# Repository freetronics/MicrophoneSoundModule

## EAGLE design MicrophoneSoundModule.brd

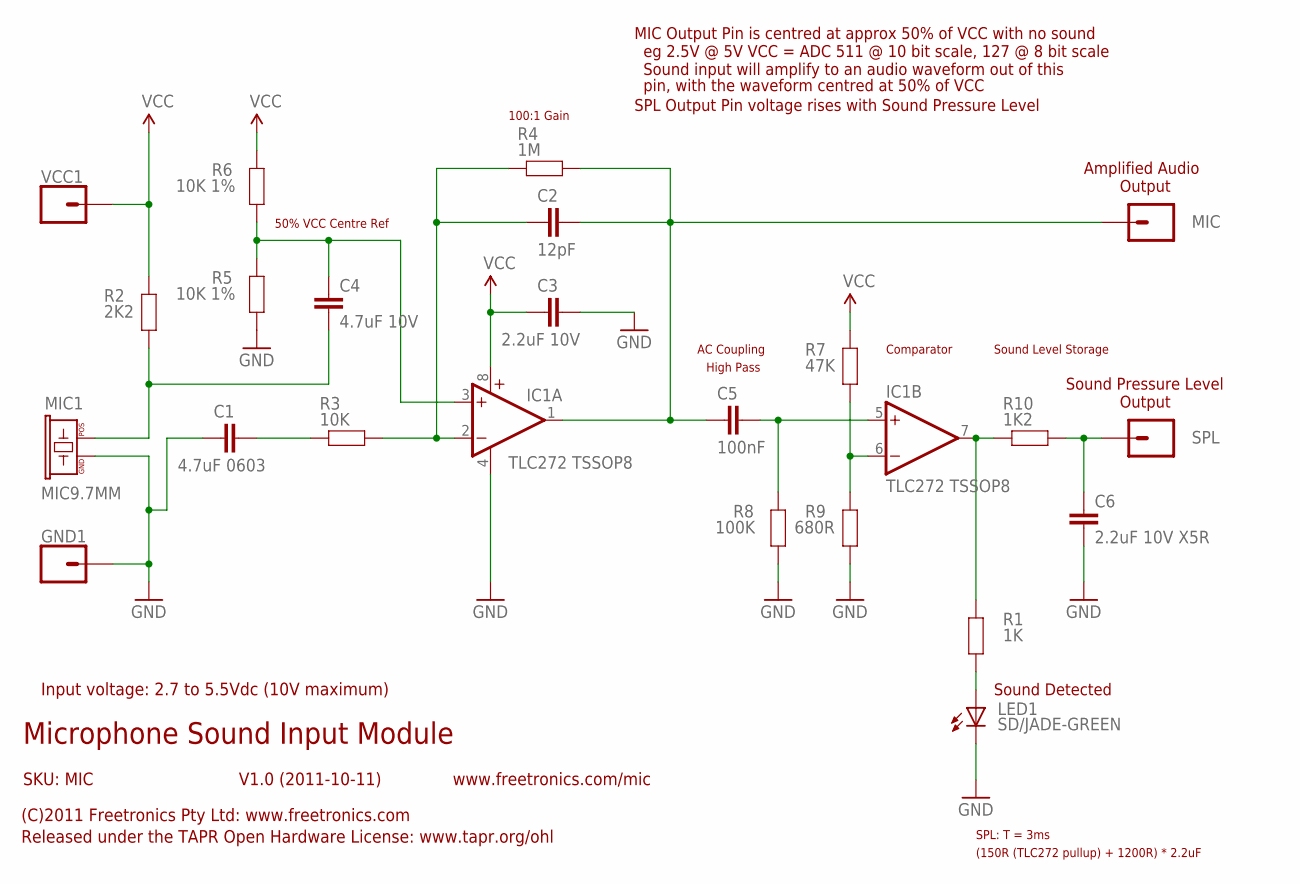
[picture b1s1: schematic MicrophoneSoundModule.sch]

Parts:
C1: 4.7uF 0603; 0603
C2: 12pF; 0603
C3: 2.2uF 10V; 0603
C4: 4.7uF 10V; 0603
C5: 100nF; 0603
C6: 2.2uF 10V X5R; 0603
GND1: M01PTH; 1X01
IC1: TLC272 TSSOP8; TSSOP8
LED1: SD/JADE-GREEN; LED-0603
MIC: M01PTH; 1X01
MIC1: MIC9.7MM; MIC-9.7MM
R1: 1K; 0603
R2: 2K2; 0603
R3: 10K; 0603
R4: 1M; 0603
R5, R6: 10K 1%; 0603
R7: 47K; 0603
R8: 100K; 0603
R9: 680R; 0603
R10: 1K2; 0603
SPL: M01PTH; 1X01
VCC1: M01PTH; 1X01

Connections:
GND: C1.1, C3.2, C6.1, GND1.1, IC1.4 (V-), LED1.C, MIC1.GND, R5.1, R8.1, R9.1
unnamed: LED1.A, R1.1
unnamed: C4.1, MIC1.POS, R2.1
unnamed: C1.2, R3.2
unnamed: C2.1, IC1.2 (-IN), R3.1, R4.2
unnamed: C2.2, C5.1, IC1.1 (OUT), MIC.1, R4.1
unnamed: C5.2, IC1.5 (+IN), R8.2
unnamed: C4.2, IC1.3 (+IN), R5.2, R6.1
unnamed: C6.2, R10.1, SPL.1
unnamed: IC1.6 (-IN), R7.1, R9.2
unnamed: IC1.7 (OUT), R1.2, R10.2
VCC: C3.1, IC1.8 (V+), R2.2, R6.2, R7.2, VCC1.1

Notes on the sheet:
Microphone Sound Input Module
V1.0 (2011-10-11)
SKU: MIC
(C)2011 Freetronics Pty Ltd: www.freetronics.com
Released under the TAPR Open Hardware License: www.tapr.org/ohl
www.freetronics.com/mic
Input voltage: 2.7 to 5.5Vdc (10V maximum)
50% VCC Centre Ref
100:1 Gain
MIC Output Pin is centred at approx 50% of VCC with no sound
eg 2.5V @ 5V VCC = ADC 511 @ 10 bit scale, 127 @ 8 bit scale
Sound input will amplify to an audio waveform out of this
pin, with the waveform centred at 50% of VCC
Amplified Audio
Comparator
AC Coupling
High Pass
Sound Level Storage
Sound Pressure Level
Output
Sound Detected
SPL Output Pin voltage rises with Sound Pressure Level
SPL: T = 3ms
(150R (TLC272 pullup) + 1200R) * 2.2uF

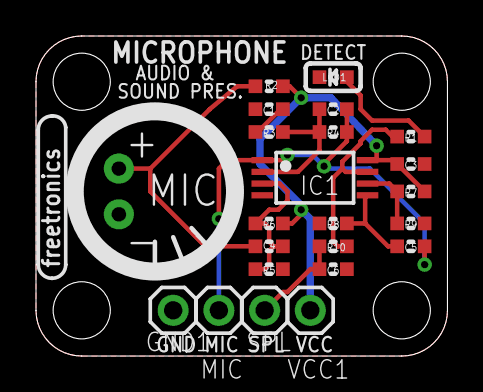
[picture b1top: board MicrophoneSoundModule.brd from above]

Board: 2 copper layers, 22.9 x 17.8 mm, 23 parts (0 on the bottom side), 12 nets.

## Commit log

2011-10-13 First push, pcb underway
2011-10-13 pcb in progress
2011-10-14 pcb nearly complete
2011-10-14 v1.0 release
2011-12-12 Schematic and Reference PDF renamed
2013-05-24 Reorient AC decoupling capacitors to reduce noise
2013-05-24 Bump revision, add revision to PCB, update schematic PDF
